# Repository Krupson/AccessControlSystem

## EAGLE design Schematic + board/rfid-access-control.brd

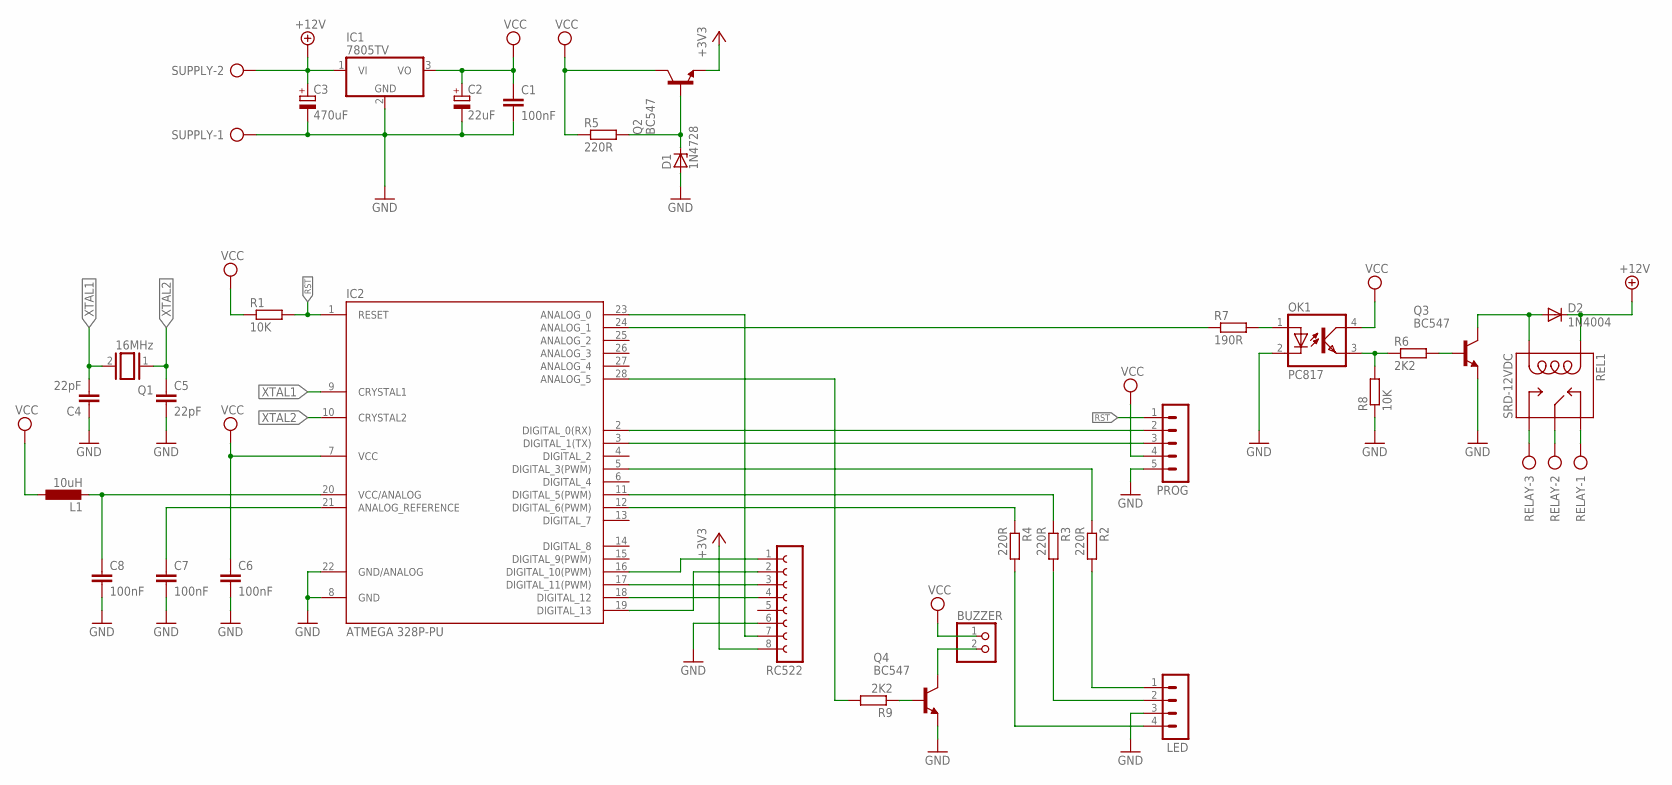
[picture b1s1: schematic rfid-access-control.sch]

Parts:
BUZZER: PINHD-1X2; 1X02
C1, C6, C7, C8: 100nF; C025-025X050
C2: 22uF; E2,5-7
C3: 470uF; E2,5-7
C4, C5: 22pF; C025-025X050
D1: 1N4728; DO41Z10
D2: 1N4004; DO41-10
IC1: 7805TV; TO220V
IC2: ATMEGA 328P-PU; DIL28-3
L1: 10uH; 0207/7
LED: MA04-1
OK1: PC817; DIL04
PROG: MA05-1
Q1: 16MHz; QS
Q2, Q3, Q4: BC547; TO92
R1, R8: 10K; 0207/7
R2, R3, R4, R5: 220R; 0207/7
R6, R9: 2K2; 0207/7
R7: 190R; 0207/7
RC522: FE08-1; FE08
REL1: SRD-12VDC; SRD-05VDC-SL-C
RELAY: AK500/3
SUPPLY: AK500/2

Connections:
+3V3: Q2.1 (E), RC522.8
+12V: C3.+, D2.C, IC1.1 (VI), REL1.COIL1, SUPPLY.2
GND: C1.2, C2.-, C3.-, C4.1, C5.2, C6.2, C7.2, C8.2, D1.A, IC1.2 (GND), IC2.8 (GND), IC2.22 (GND/ANALOG), LED.3, OK1.2 (C), PROG.5, Q3.1 (E), Q4.1 (E), R8.1, RC522.6, SUPPLY.1
unnamed: IC2.16 (DIGITAL_10(PWM)), RC522.1
unnamed: C8.1, IC2.20 (VCC/ANALOG), L1.2
unnamed: C7.1, IC2.21 (ANALOG_REFERENCE)
unnamed: IC2.19 (DIGITAL_13), RC522.2
unnamed: IC2.17 (DIGITAL_11(PWM)), RC522.3
unnamed: IC2.18 (DIGITAL_12), RC522.4
unnamed: IC2.23 (ANALOG_0), RC522.7
unnamed: LED.2, R3.2
unnamed: LED.1, R2.2
unnamed: LED.4, R4.2
unnamed: IC2.5 (DIGITAL_3(PWM)), R2.1
unnamed: IC2.11 (DIGITAL_5(PWM)), R3.1
unnamed: IC2.12 (DIGITAL_6(PWM)), R4.1
unnamed: IC2.28 (ANALOG_5), R9.2
unnamed: D1.C, Q2.2 (B), R5.2
unnamed: REL1.SWCLOSED (SWCLOSE), RELAY.1
unnamed: D2.A, Q3.3 (C), REL1.COIL0
unnamed: REL1.SWCOMMON, RELAY.2
unnamed: IC2.3 (DIGITAL_1(TX)), PROG.3
unnamed: IC2.2 (DIGITAL_0(RX)), PROG.2
unnamed: REL1.SWOPEN, RELAY.3
unnamed: Q3.2 (B), R6.2
unnamed: OK1.3 (EMIT), R6.1, R8.2
unnamed: OK1.1 (A), R7.2
unnamed: IC2.24 (ANALOG_1), R7.1
unnamed: Q4.2 (B), R9.1
unnamed: BUZZER.2, Q4.3 (C)
RST: IC2.1 (RESET), PROG.1, R1.2
VCC: BUZZER.1, C1.1, C2.+, C6.1, IC1.3 (VO), IC2.7 (VCC), L1.1, OK1.4 (COL), PROG.4, Q2.3 (C), R1.1, R5.1
XTAL1: C4.2, IC2.9 (CRYSTAL1), Q1.2
XTAL2: C5.1, IC2.10 (CRYSTAL2), Q1.1

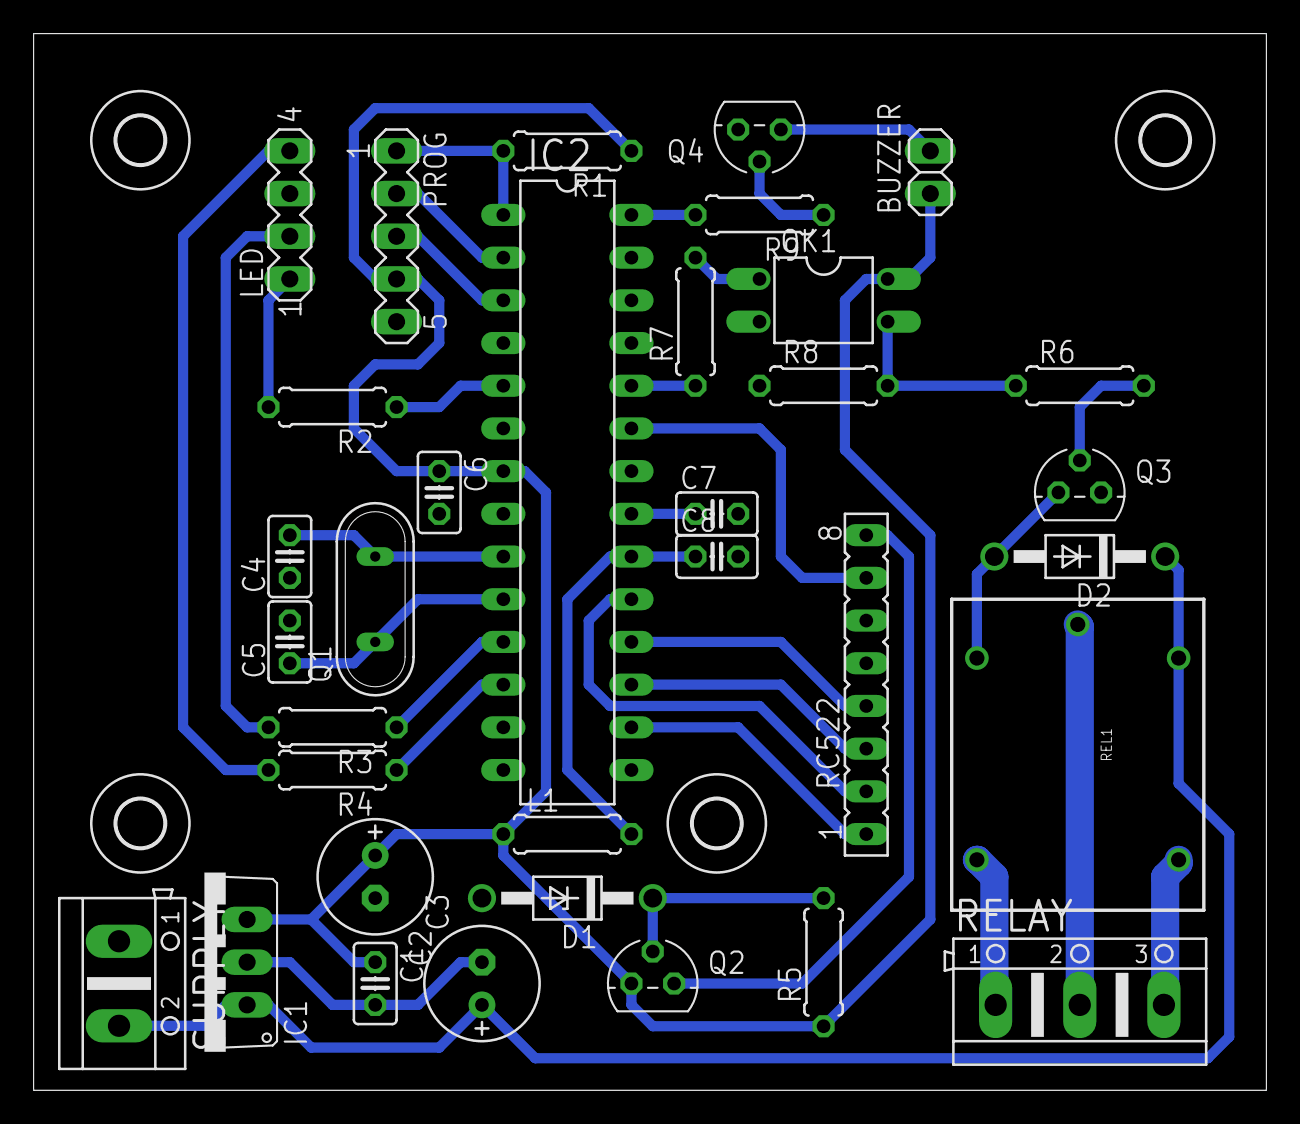
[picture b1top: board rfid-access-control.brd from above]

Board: 2 copper layers, 73.3 x 62.9 mm, 38 parts (0 on the bottom side), 34 nets.

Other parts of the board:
U$1, U$2, U$3, U$4: 2,8
